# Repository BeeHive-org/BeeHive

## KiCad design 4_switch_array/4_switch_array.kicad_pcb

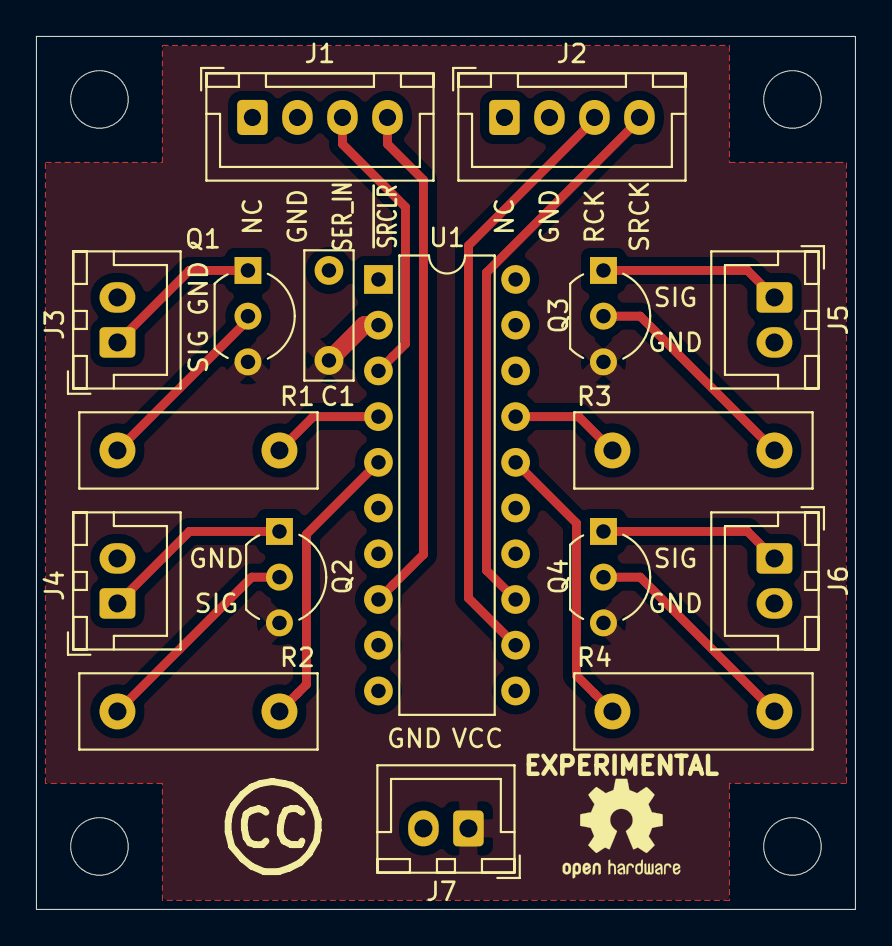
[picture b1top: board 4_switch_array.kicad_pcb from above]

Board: 2 copper layers, 45.5 x 48.5 mm, 17 parts (0 on the bottom side), 18 nets.

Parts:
C1: 100nF; C_Disc_D7.0mm_W2.5mm_P5.00mm
J1, J2: Conn_01x04; JST_XH_B4B-XH-A_1x04_P2.50mm_Vertical
J3, J4, J5, J6, J7: Conn_01x02; JST_XH_B2B-XH-A_1x02_P2.50mm_Vertical
Q1, Q2, Q3, Q4: Q_NPN_EBC; TO-92_Inline_Wide
R1, R2, R3, R4: 270; R_Box_L13.0mm_W4.0mm_P9.00mm
U1: TPIC6595; DIP-20_W7.62mm

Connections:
+5V: C1.1, J7.1, Q1.3, Q2.3, Q3.3, Q4.3, U1.2
DRAIN0: R1.1, U1.4
DRAIN1: R2.1, U1.5
DRAIN6: R4.1, U1.16
DRAIN7: R3.1, U1.17
GND: C1.2, J1.2, J2.2, J3.2, J4.2, J5.2, J6.2, J7.2, U1.1, U1.9, U1.10, U1.11, U1.19, U1.20
unnamed: J3.1, Q1.1
unnamed: J4.1, Q2.1
unnamed: J5.1, Q3.1
unnamed: J6.1, Q4.1
unnamed: Q1.2, R1.2
unnamed: Q2.2, R2.2
unnamed: Q3.2, R3.2
unnamed: Q4.2, R4.2
RCLK: J2.3, U1.12
SER_IN: J1.3, U1.3
SRCK: J2.4, U1.13
SRCLR: J1.4, U1.8

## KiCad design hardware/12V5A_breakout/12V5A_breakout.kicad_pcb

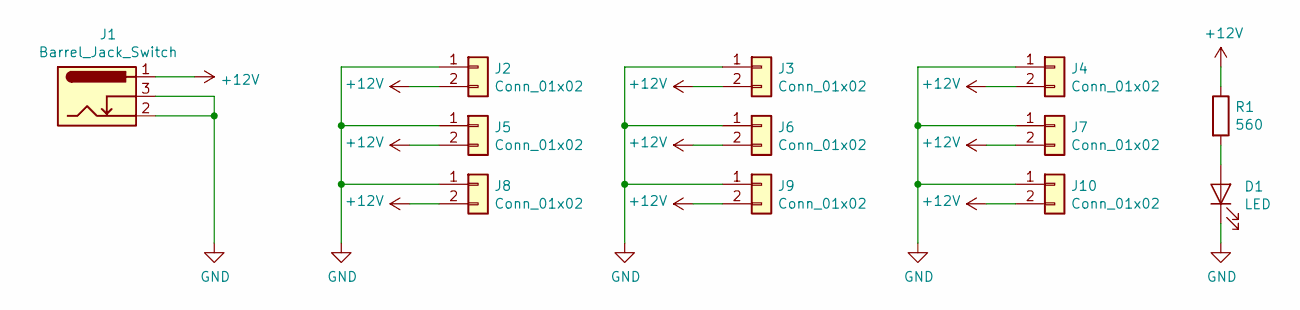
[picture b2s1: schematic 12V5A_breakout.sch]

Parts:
D1: LED; LED_D3.0mm
J1: Barrel_Jack_Switch; BarrelJack_Horizontal
J2, J3, J4, J5, J6, J7, J8, J9, J10: Conn_01x02; JST_XH_B2B-XH-A_1x02_P2.50mm_Vertical
R1: 560; R_Box_L13.0mm_W4.0mm_P9.00mm

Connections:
+12V: J1.1, J2.2, J3.2, J4.2, J5.2, J6.2, J7.2, J8.2, J9.2, J10.2, R1.1
GND: D1.1 (K), J1.2, J1.3, J2.1, J3.1, J4.1, J5.1, J6.1, J7.1, J8.1, J9.1, J10.1; also elsewhere on the board
unnamed 2: D1.2 (A), R1.2; also elsewhere on the board

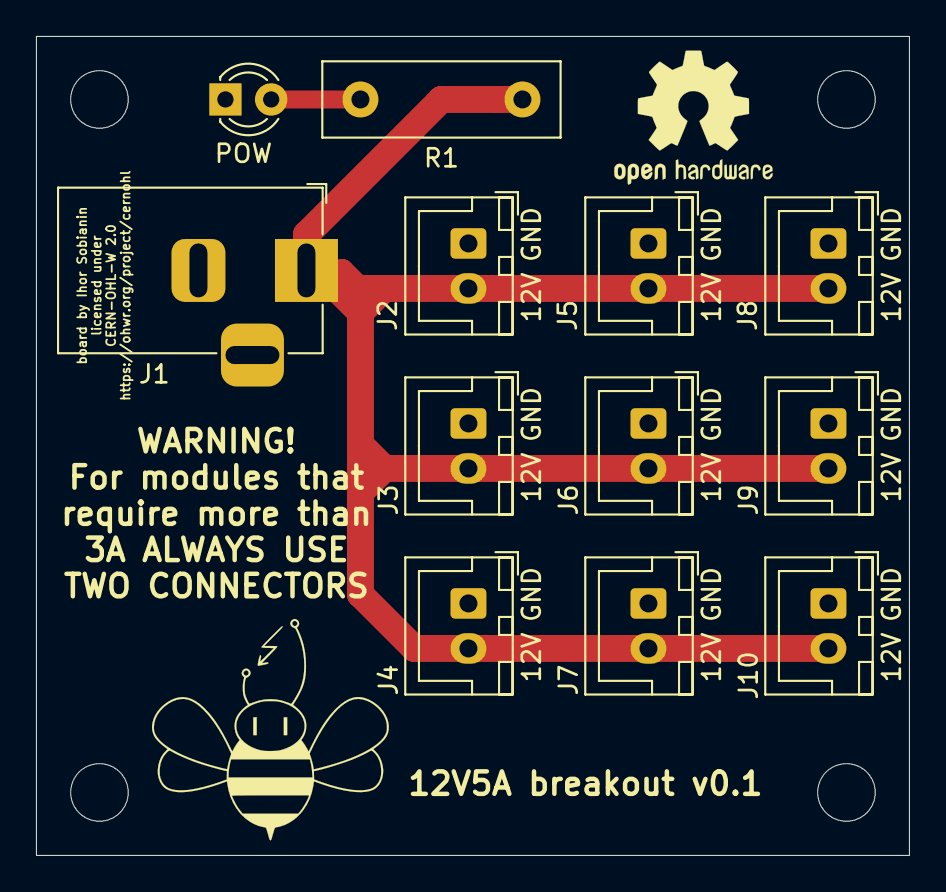
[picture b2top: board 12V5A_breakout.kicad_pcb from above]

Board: 2 copper layers, 48.5 x 45.5 mm, 12 parts (0 on the bottom side), 3 nets.

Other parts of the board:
POW: LED; LED_D3.0mm

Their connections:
GND: POW.1; also elsewhere on the board
unnamed 2: POW.2; also elsewhere on the board

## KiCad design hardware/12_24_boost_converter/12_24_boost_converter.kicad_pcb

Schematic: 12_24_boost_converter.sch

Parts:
C1, C2: 100nF; C_Disc_D5.1mm_W3.2mm_P5.00mm
C3: 22µF; CP_Radial_D5.0mm_P2.00mm
D1: 1N5822; D_DO-201AD_P15.24mm_Horizontal
D2: LED; LED_D3.0mm
J1, J2, J3: Conn_01x02; JST_XH_B2B-XH-A_1x02_P2.50mm_Vertical
L1: 33µH; L_Radial_D10.0mm_P5.00mm_Neosid_SD12_style3
Q1: IRFZ24NPBF; TO-220-3_Vertical
R1, R2, R3: 47; R_Axial_DIN0411_L9.9mm_D3.6mm_P12.70mm_Horizontal
R4: 1k; R_Axial_DIN0411_L9.9mm_D3.6mm_P12.70mm_Horizontal
R5: 560; R_Axial_DIN0411_L9.9mm_D3.6mm_P12.70mm_Horizontal
U1: LM555xM; DIP-8_W7.62mm_LongPads

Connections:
+12V: J1.1, J2.1, L1.1, R1.1, R5.2, U1.4 (R), U1.8 (VCC)
+24V: C3.1, D1.1 (K), J3.1; also elsewhere on the board
GND: C1.1, C2.1, C3.2, D2.1, J1.2, J2.2, J3.2, Q1.3 (S), R4.2, U1.1 (GND); also elsewhere on the board
unnamed: C1.2, R2.1, U1.2 (TR), U1.6 (THR)
unnamed: C2.2, U1.5 (CV)
unnamed: D1.2 (A), L1.2, Q1.2 (D)
unnamed: D2.2, R5.1
unnamed: Q1.1 (G), R3.1, R4.1
unnamed: R1.2, R2.2, U1.7 (DIS)
unnamed: R3.2, U1.3 (Q)

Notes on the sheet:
LM555's pin 3 frequency depends on pin 7 and 6 resistors values and pin 2 capacitor value, provided pin 5 capacitor remains constant. This configuration provides about 100kHz frequency. It can also be achieved with another set of components. The choice of components depends solely on what is more c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
***

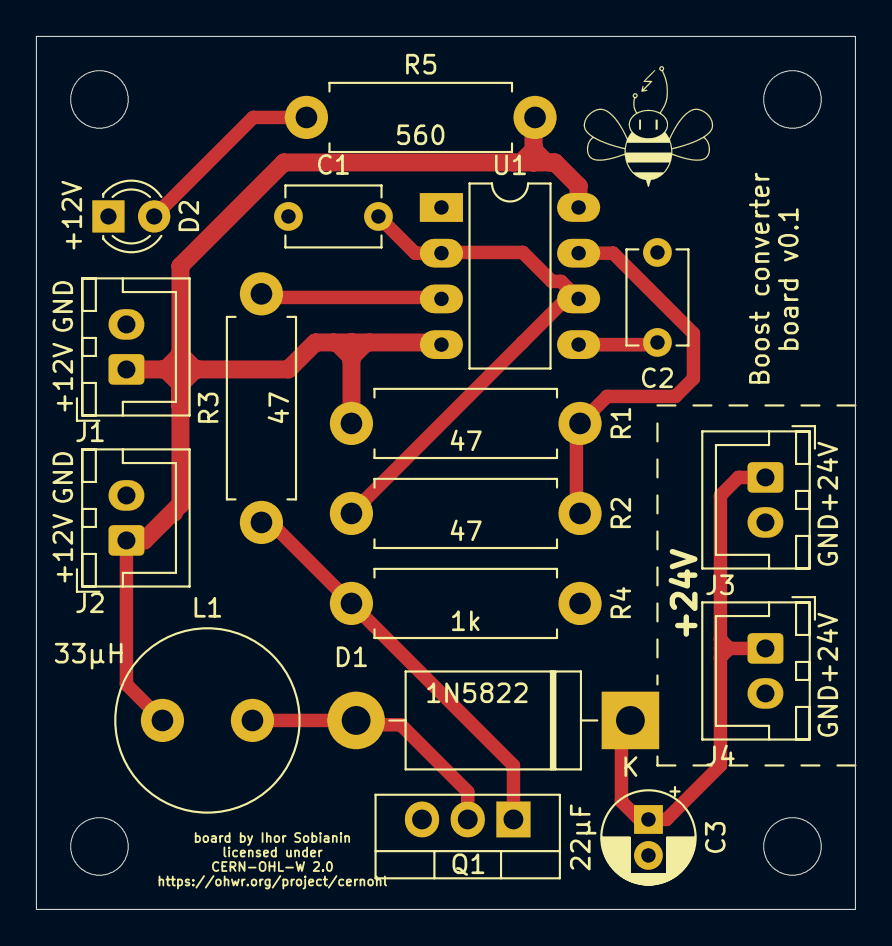
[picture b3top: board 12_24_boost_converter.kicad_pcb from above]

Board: 2 copper layers, 45.5 x 48.5 mm, 17 parts (0 on the bottom side), 10 nets.

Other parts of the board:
J4: Conn_01x02; JST_XH_B2B-XH-A_1x02_P2.50mm_Vertical

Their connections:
+24V: J4.1; also elsewhere on the board
GND: J4.2; also elsewhere on the board

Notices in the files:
hardware/12V5A_breakout/12V5A_breakout.kicad_pcb:
licensed under
CERN-OHL-W 2.0
